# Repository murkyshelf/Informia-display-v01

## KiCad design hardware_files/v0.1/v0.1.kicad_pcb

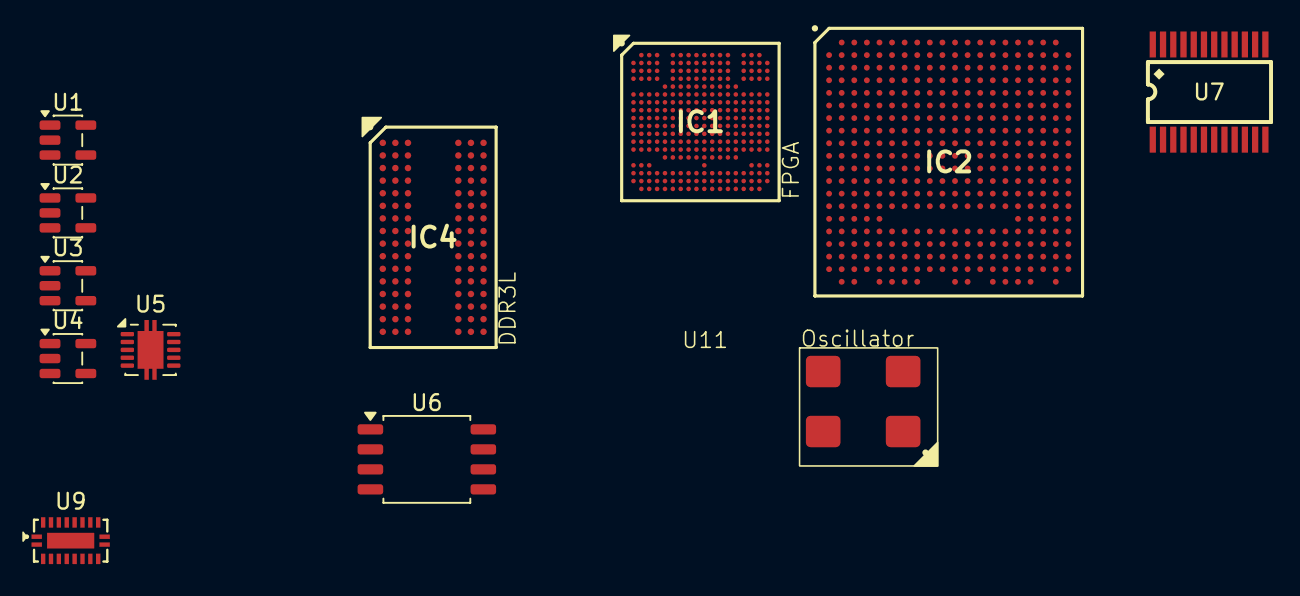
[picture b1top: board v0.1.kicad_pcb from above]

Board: 2 copper layers, 12 parts (0 on the bottom side), 25 nets, no tracks yet.

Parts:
IC1: LFE5UM5G-85F-8MG285C; BGA285C50P18X18_1000X1000X130
IC2: LFE5UM5G-85F-8BG381C; BGA381C80P20X20_1700X1700X176
IC4: MT41K128M16JT-125_K; BGA96C80P9X16_800X1400X120
U1, U2, U3: TLV62569DBV; SOT-23-5
U4: LP5907MFX-1.2; SOT-23-5
U5: TPS51200DRC; VSON-10-1EP_3x3mm_P0.5mm_EP1.65x2.4mm
U6: W25Q128JVS; SOIC-8_5.3x5.3mm_P1.27mm
U7: TPD12S016PWR; TSSOP-24_L7.8-W4.4-P0.65-LS6.4-BL
U9: HD3SS3212IRKSR; DHVQFN-20_L4.5-W2.5-P0.50-BL-EP
U11: SIT8008BI-83-33E-100.000000X; 4-PQFN

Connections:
+1V2: IC1.D8 (VCC_1), IC1.D9 (VCC_2), IC1.D10 (VCC_3), IC1.D11 (VCC_4), IC1.J4 (VCC_5), IC1.J5 (VCC_6), IC1.J14 (VCC_7), IC1.J15 (VCC_8), IC1.M4 (VCC_9), IC1.M15 (VCC_10), IC1.P7 (VCC_11), IC1.P9 (VCC_12), IC1.P11 (VCC_13)
+1V2_cleane: IC1.P10 (VCCA0_1), IC1.R10 (VCCA0_2), IC1.T5 (VCCHTX1_D0CH1), IC1.U6 (VCCHRX1_D0CH1), IC1.U8 (VCCHRX0_D0CH0), IC1.U12 (VCCHTX0_D0CH0), U4.5 (OUT)
+2V5_clean: IC1.E6 (VCCAUX_1), IC1.E13 (VCCAUX_2), IC1.N6 (VCCAUX_3), IC1.P5 (VCCAUXA0_1), IC1.P13 (VCCAUX_4), IC1.R3 (VCCAUXA0_2)
+3V3: IC1.D7 (VCCIO1), IC1.D12 (VCCIO0), IC1.G5 (VCCIO2_1), IC1.G14 (VCCIO7_1), IC1.H5 (VCCIO2_2), IC1.H14 (VCCIO7_2), IC1.M5 (VCCIO3_1), IC1.M14 (VCCIO6_1), IC1.N5 (VCCIO3_2), IC1.N13 (VCCIO8_1), IC1.N14 (VCCIO6_2), IC1.P14 (VCCIO8_2), U6.8 (VCC), U9.6 (VCC)
+5V: U1.4 (VIN), U2.4 (VIN), U3.4 (VIN), U7.11 (VCC5V), U7.24 (VCCA)
GND: U1.2 (GND), U2.2 (GND), U3.2 (GND), U4.2 (GND), U5.4 (GND), U5.8 (GND), U5.11 (GND), U6.4 (GND), U7.6 (GND), U7.14 (GND), U7.19 (GND), U9.5 (GND), U9.11 (GND), U9.20 (GND), U9.21 (GND), U11.2 (GND_2)
unnamed: IC2.B7 (GND[85]), IC2.B14 (GND_2), IC2.C19 (GND_3), IC2.D4 (GND_4), IC2.F7 (GND_5), IC2.F8 (GND_6), IC2.F13 (GND_7), IC2.F14 (GND_8), IC2.G4 (GND_9), IC2.G6 (GND_10), IC2.G7 (GND_11), IC2.G8 (GND_12), IC2.G9 (GND_13), IC2.G10 (GND_14), IC2.G11 (GND_15), IC2.G12 (GND_16), IC2.G13 (GND_17), IC2.G14 (GND_18), IC2.G15 (GND_19), IC2.G17 (GND_20), IC2.H19 (GND_21), IC2.J2 (GND_22), IC2.J7 (GND_23), IC2.J9 (GND_24), IC2.J10 (GND_25), IC2.J11 (GND_26), IC2.J12 (GND_27), IC2.J14 (GND_28), IC2.K6 (GND_29), IC2.K7 (GND_30), IC2.K9 (GND_31), IC2.K10 (GND_32), IC2.K11 (GND_33), IC2.K12 (GND_34), IC2.K14 (GND_35), IC2.K15 (GND_36), IC2.L9 (GND_37), IC2.L10 (GND_38), IC2.L11 (GND_39), IC2.L12 (GND_40), IC2.M2 (GND_41), IC2.M7 (GND_42), IC2.M9 (GND_43), IC2.M10 (GND_44), IC2.M11 (GND_45), IC2.M12 (GND_46), IC2.M14 (GND_47), IC2.M16 (GND_48), IC2.N6 (GND_49), IC2.N7 (GND_50), IC2.N14 (GND_51), IC2.N15 (GND_52), IC2.P7 (GND_53), IC2.P8 (GND_54), IC2.P11 (GND_55), IC2.P12 (GND_56), IC2.P13 (GND_57), IC2.P14 (GND_58), IC2.R19 (GND_59), IC2.U7 (GND_60), IC2.U8 (GND_61), IC2.U9 (GND_62), IC2.U10 (GND_63), IC2.U11 (GND_64), IC2.U12 (GND_65), IC2.U13 (GND_66), IC2.U14 (GND_67), IC2.V5 (GND_68), IC2.V6 (GND_69), IC2.V7 (GND_70), IC2.V8 (GND_71), IC2.V9 (GND_72), IC2.V12 (GND_73), IC2.V13 (GND_74), IC2.V14 (GND_75), IC2.V15 (GND_76), IC2.V16 (GND_77), IC2.V19 (GND_78), IC2.V20 (GND_79), IC2.W6 (GND_80), IC2.W7 (GND_81), IC2.W12 (GND_82), IC2.W15 (GND_83), IC2.W16 (GND_84), IC2.W19 (GND_85)
unnamed: IC2.W10 (RESERVED[2]), IC2.W11 (RESERVED_2)
unnamed: IC2.T6 (VCCA0[2]), IC2.U6 (VCCA0_2)
unnamed: IC2.T15 (VCCA1[2]), IC2.U15 (VCCA1_2)
unnamed: IC2.V10 (VCCAUXA0[2]), IC2.V11 (VCCAUXA0_2)
unnamed: IC2.V17 (VCCAUXA1[2]), IC2.V18 (VCCAUXA1_2)
unnamed: IC2.F6 (VCCAUX[4]), IC2.F15 (VCCAUX_2), IC2.P6 (VCCAUX_3), IC2.P15 (VCCAUX_4)
unnamed: IC2.F9 (VCCIO0[2]), IC2.F10 (VCCIO0_2)
unnamed: IC2.F11 (VCCIO1[2]), IC2.F12 (VCCIO1_2)
unnamed: IC2.H14 (VCCIO2[3]), IC2.H15 (VCCIO2_2), IC2.J15 (VCCIO2_3)
unnamed: IC2.L14 (VCCIO3[3]), IC2.L15 (VCCIO3_2), IC2.M15 (VCCIO3_3)
unnamed: IC2.L6 (VCCIO6[3]), IC2.L7 (VCCIO6_2), IC2.M6 (VCCIO6_3)
unnamed: IC2.H6 (VCCIO7[3]), IC2.H7 (VCCIO7_2), IC2.J6 (VCCIO7_3)
unnamed: IC2.P9 (VCCIO8[2]), IC2.P10 (VCCIO8_2)
unnamed: IC2.H8 (VCC[20]), IC2.H9 (VCC_2), IC2.H10 (VCC_3), IC2.H11 (VCC_4), IC2.H12 (VCC_5), IC2.H13 (VCC_6), IC2.J8 (VCC_7), IC2.J13 (VCC_8), IC2.K8 (VCC_9), IC2.K13 (VCC_10), IC2.L8 (VCC_11), IC2.L13 (VCC_12), IC2.M8 (VCC_13), IC2.M13 (VCC_14), IC2.N8 (VCC_15), IC2.N9 (VCC_16), IC2.N10 (VCC_17), IC2.N11 (VCC_18), IC2.N12 (VCC_19), IC2.N13 (VCC_20)
unnamed: IC4.A1 (VDDQ[9]), IC4.A8 (VDDQ_2), IC4.C1 (VDDQ_3), IC4.C9 (VDDQ_4), IC4.D2 (VDDQ_5), IC4.E9 (VDDQ_6), IC4.F1 (VDDQ_7), IC4.H2 (VDDQ_8), IC4.H9 (VDDQ_9)
unnamed: IC4.B2 (VDD[9]), IC4.D9 (VDD_2), IC4.G7 (VDD_3), IC4.K2 (VDD_4), IC4.K8 (VDD_5), IC4.N1 (VDD_6), IC4.N9 (VDD_7), IC4.R1 (VDD_8), IC4.R9 (VDD_9)
unnamed: IC4.B1 (VSSQ[9]), IC4.B9 (VSSQ_2), IC4.D1 (VSSQ_3), IC4.D8 (VSSQ_4), IC4.E2 (VSSQ_5), IC4.E8 (VSSQ_6), IC4.F9 (VSSQ_7), IC4.G1 (VSSQ_8), IC4.G9 (VSSQ_9)
unnamed: IC4.A9 (VSS[12]), IC4.B3 (VSS_2), IC4.E1 (VSS_3), IC4.G8 (VSS_4), IC4.J2 (VSS_5), IC4.J8 (VSS_6), IC4.M1 (VSS_7), IC4.M9 (VSS_8), IC4.P1 (VSS_9), IC4.P9 (VSS_10), IC4.T1 (VSS_11), IC4.T9 (VSS_12)
